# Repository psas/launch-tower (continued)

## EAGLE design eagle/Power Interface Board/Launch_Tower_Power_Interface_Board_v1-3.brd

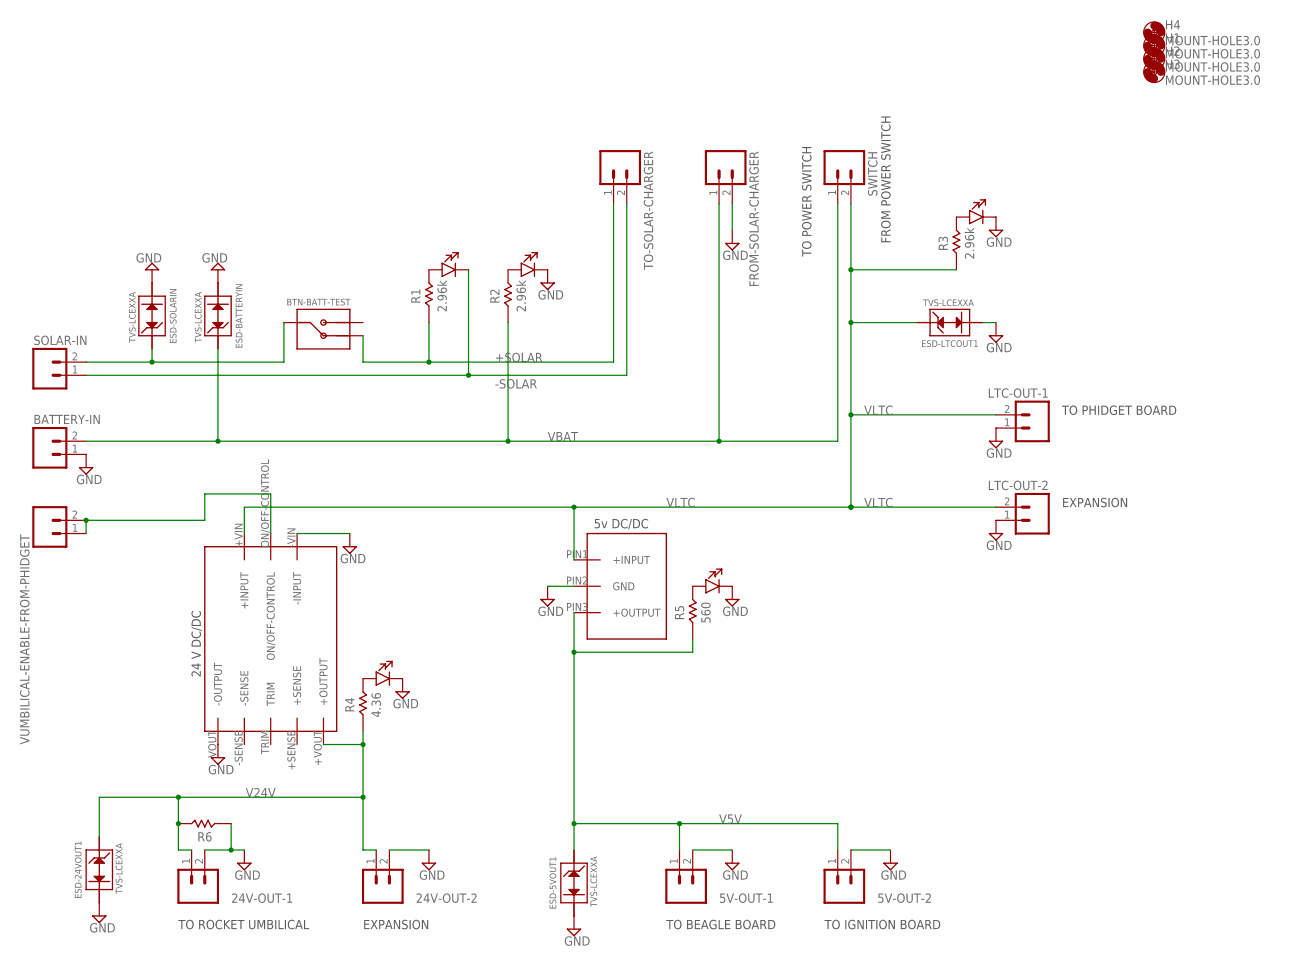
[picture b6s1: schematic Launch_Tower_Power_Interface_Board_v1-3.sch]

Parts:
5V-OUT-1, 5V-OUT-2, 24V-OUT-1, 24V-OUT-2: M025MM; SCREWTERMINAL-5MM-2
BATTERY-IN: M025MM; SCREWTERMINAL-5MM-2
BTN-BATT-TEST: BUTTON-107-3006-EVX; BUTTON-1
ESD-5VOUT1, ESD-24VOUT1: TVS-LCEXXA; D0-201
ESD-BATTERYIN: TVS-LCEXXA; D0-201
ESD-LTCOUT1: TVS-LCEXXA; D0-201
ESD-SOLARIN: TVS-LCEXXA; D0-201
FROM-SOLAR-CHARGER: M025MM; SCREWTERMINAL-5MM-2
H1, H2, H3, H4: MOUNT-HOLE3.0; 3,0
LED-5V-DC/DC, LED-24V-DC/DC: LED-550-XX04; LED-550
LED-BATTERY-IN: LED-550-XX04; LED-550
LED-SOLAR-IN: LED-550-XX04; LED-550
LED-SWITCH-IN: LED-550-XX04; LED-550
LTC-OUT-1, LTC-OUT-2: M025MM; SCREWTERMINAL-5MM-2
R1, R2, R3: 2.96k; 0805
R4: 4.36; 0805
R5: 560; 0805
R6: RESISTOR-0805; 0805
SOLAR-IN: M025MM; SCREWTERMINAL-5MM-2
SWITCH: M025MM; SCREWTERMINAL-5MM-2
TO-SOLAR-CHARGER: M025MM; SCREWTERMINAL-5MM-2
U$1: DC/DC_CONV_24V; UWE
U$2: DC/DC_CONV_5V; OKI-SIP
VUMBILICAL-ENABLE-FROM-PHIDGET: M023.5MM; SCREWTERMINAL-3.5MM-2

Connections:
+SOLAR: BTN-BATT-TEST.NC, R1.ANODE, TO-SOLAR-CHARGER.1
-SOLAR: LED-SOLAR-IN.CATHODE, SOLAR-IN.1, TO-SOLAR-CHARGER.2
GND: 5V-OUT-1.2, 5V-OUT-2.2, 24V-OUT-1.2, 24V-OUT-2.2, BATTERY-IN.1, ESD-5VOUT1.CATHODE, ESD-24VOUT1.CATHODE, ESD-BATTERYIN.CATHODE, ESD-LTCOUT1.CATHODE, ESD-SOLARIN.CATHODE, FROM-SOLAR-CHARGER.2, LED-5V-DC/DC.CATHODE, LED-24V-DC/DC.CATHODE, LED-BATTERY-IN.CATHODE, LED-SWITCH-IN.CATHODE, LTC-OUT-1.1, LTC-OUT-2.1, R6.ANODE, U$1.-VIN (-INPUT), U$1.-VOUT (-OUTPUT), U$2.PIN2 (GND)
GPIO: U$1.ON/OFF-CONTROL, VUMBILICAL-ENABLE-FROM-PHIDGET.1, VUMBILICAL-ENABLE-FROM-PHIDGET.2
unnamed: LED-SOLAR-IN.ANODE, R1.CATHODE
unnamed: LED-BATTERY-IN.ANODE, R2.CATHODE
unnamed: LED-SWITCH-IN.ANODE, R3.CATHODE
unnamed: LED-5V-DC/DC.ANODE, R5.CATHODE
unnamed: LED-24V-DC/DC.ANODE, R4.CATHODE
unnamed: BTN-BATT-TEST.COMMON, ESD-SOLARIN.ANODE, SOLAR-IN.2
V5V: 5V-OUT-1.1, 5V-OUT-2.1, ESD-5VOUT1.ANODE, R5.ANODE, U$2.PIN3 (+OUTPUT)
V24V: 24V-OUT-1.1, 24V-OUT-2.1, ESD-24VOUT1.ANODE, R4.ANODE, R6.CATHODE, U$1.+VOUT (+OUTPUT)
VBAT: BATTERY-IN.2, ESD-BATTERYIN.ANODE, FROM-SOLAR-CHARGER.1, R2.ANODE, SWITCH.1
VLTC: ESD-LTCOUT1.ANODE, LTC-OUT-1.2, LTC-OUT-2.2, R3.ANODE, SWITCH.2, U$1.+VIN (+INPUT), U$2.PIN1 (+INPUT)

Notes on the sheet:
5v DC/DC
TO POWER SWITCH
FROM POWER SWITCH
EXPANSION
TO PHIDGET BOARD
TO BEAGLE BOARD
TO IGNITION BOARD
24 V DC/DC
TO ROCKET UMBILICAL

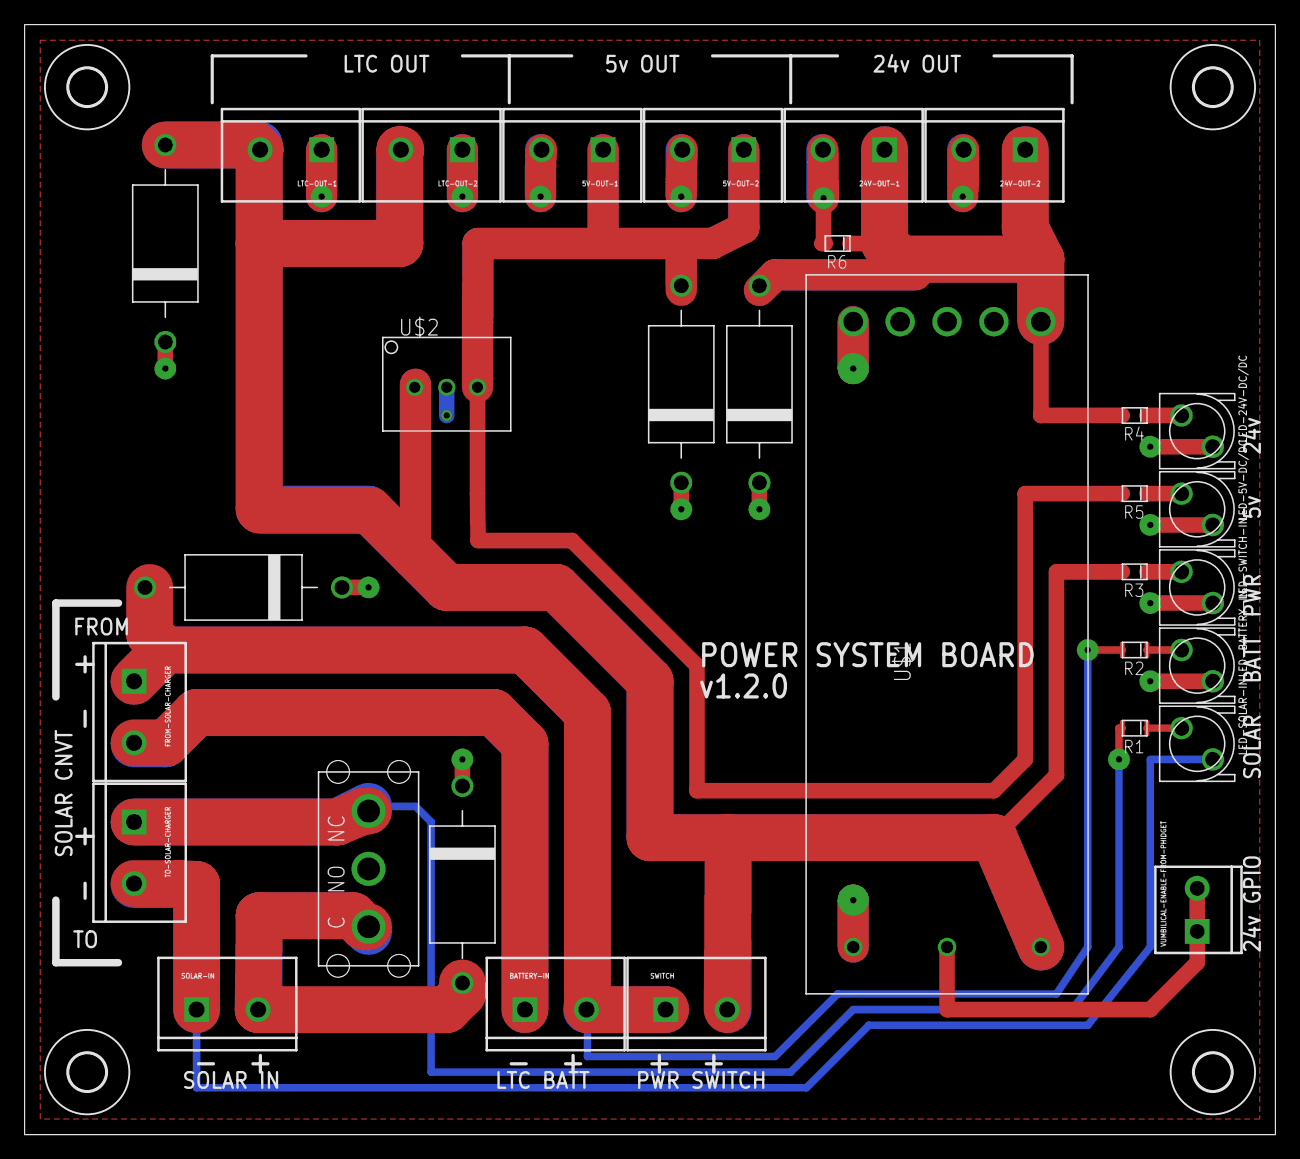
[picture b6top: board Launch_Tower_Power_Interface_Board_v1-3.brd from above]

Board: 2 copper layers, 101.6 x 90.2 mm, 35 parts (0 on the bottom side), 14 nets.

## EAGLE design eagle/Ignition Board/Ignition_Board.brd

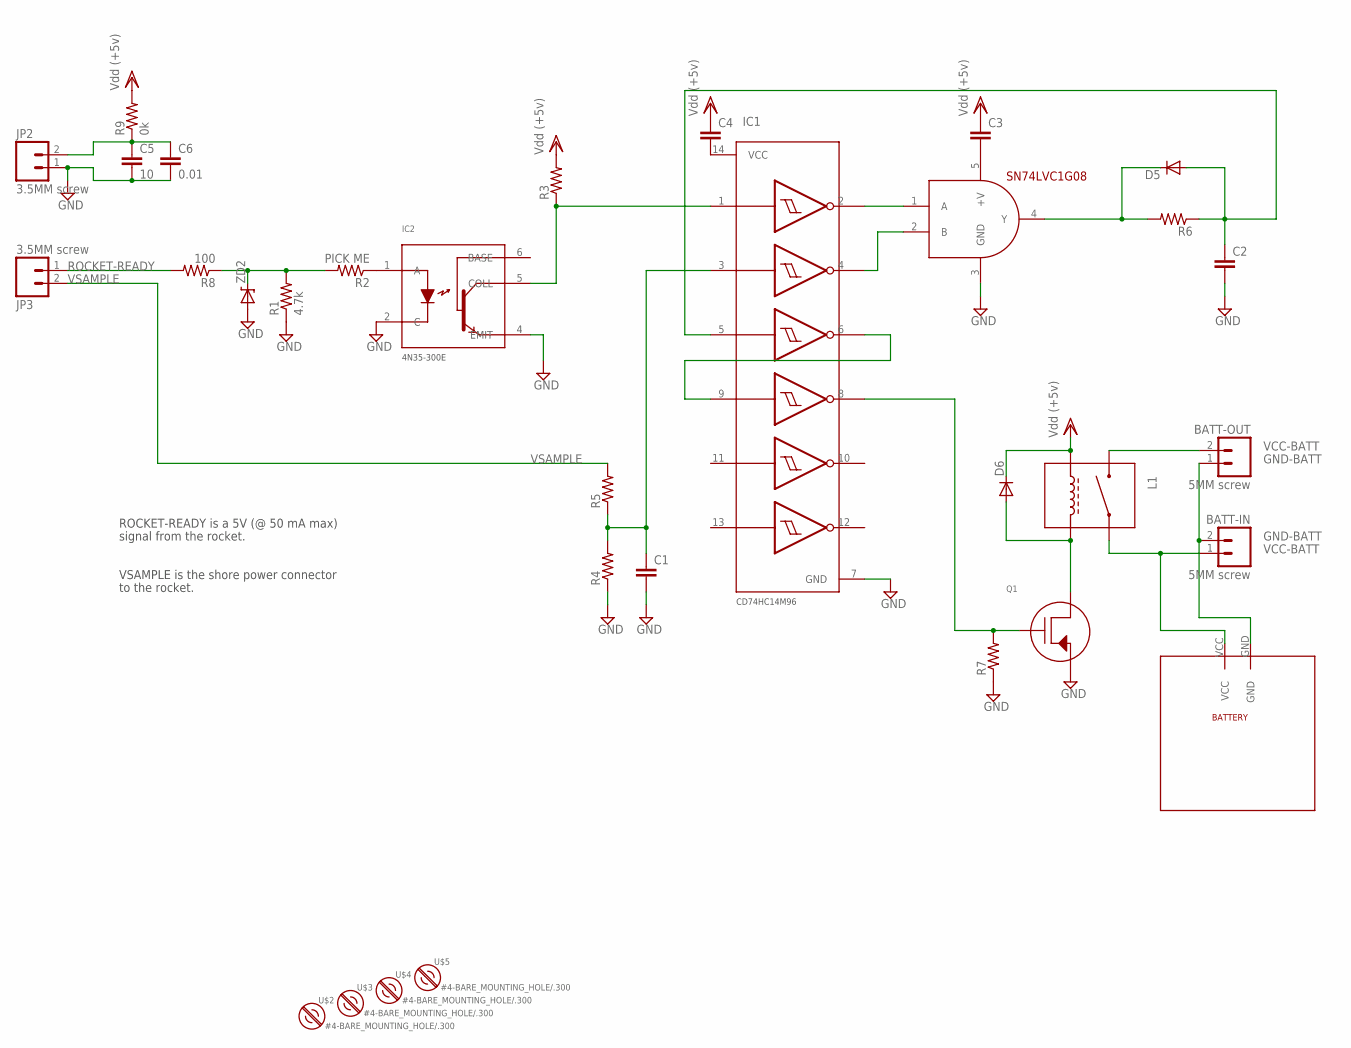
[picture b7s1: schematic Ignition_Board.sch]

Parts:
BATT-IN: 5MM screw; SCREWTERMINAL-5MM-2
BATT-OUT: 5MM screw; SCREWTERMINAL-5MM-2
C1, C2, C3, C4: C-EU0805-B-NOSILK; 0805-B-NOSILK
C5: 10; 0805-B-NOSILK
C6: 0.01; 0805-B-NOSILK
D5, D6: DIODEPTH; DIODE-1N4001
IC1: INVERT GATES; INVERTSOIC14
IC2: OPTOISOLATOR; 4N35-300E
JP2, JP3: 3.5MM screw; SCREWTERMINAL-3.5MM-2
L1: RELAY; G5T-1A
Q1: NMOSFET; FETSO-8
R1: 4.7k; 0805-B-NOSILK
R2: PICK ME; 0805-B-NOSILK
R3, R4, R5, R6, R7: R-US_0805-B-NOSILK; 0805-B-NOSILK
R8: 100; 0805-B-NOSILK
R9: 0k; 0805-B-NOSILK
U$1: AND GATE; SOT23-5
U$2, U$3, U$4, U$5: #4-BARE_MOUNTING_HOLE/.300; #4/.300-BARE+STD_NUT_OR_STAR_WASHER
U$6: BATTERY; BATT-1
ZD2: DIODE-ZENERPTH; DIODE-ZENER

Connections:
GND: C1.2, C2.2, C5.2, C6.2, IC1.7 (GND), IC2.2 (C), IC2.4 (EMIT), JP2.1, Q1.1 (SOURCE), R1.1, R4.1, R7.1, U$1.3 (GND), ZD2.P$2 (A)
GND-BATT: BATT-IN.2, BATT-OUT.1, U$6.GND
unnamed: IC1.4 (2Y), U$1.2 (B)
unnamed: IC1.1 (1A), IC2.5 (COLL), R3.1
unnamed: JP3.1, R8.2
unnamed: IC1.2 (1Y), U$1.1 (A)
unnamed: IC2.1 (A), R2.1
unnamed: C1.1, IC1.3 (2A), R4.2, R5.1
unnamed: C4.2, IC1.14 (VCC)
unnamed: D6.A, L1.CIN, Q1.5 (DRAIN)
unnamed: IC1.8 (4Y), Q1.4 (GATE), R7.2
unnamed: C3.2, U$1.5 (+V)
unnamed: C5.1, C6.1, JP2.2, R9.1
unnamed: D5.C, R6.2, U$1.4 (Y)
unnamed: C2.1, D5.A, IC1.5 (3A), R6.1
N-NOT2: IC1.6 (3Y), IC1.9 (4A)
ROCKET-READY: R1.2, R2.2, R8.1, ZD2.P$1 (C)
VCC-BATT: BATT-IN.1, BATT-OUT.2, L1.SW1, L1.SW2, U$6.VCC
VDD: C3.1, C4.1, D6.C, L1.COUT, R3.2, R9.2
VSAMPLE: JP3.2, R5.2

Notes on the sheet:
ROCKET-READY is a 5V (@ 50 mA max)
signal from the rocket.
VSAMPLE is the shore power connector
to the rocket.

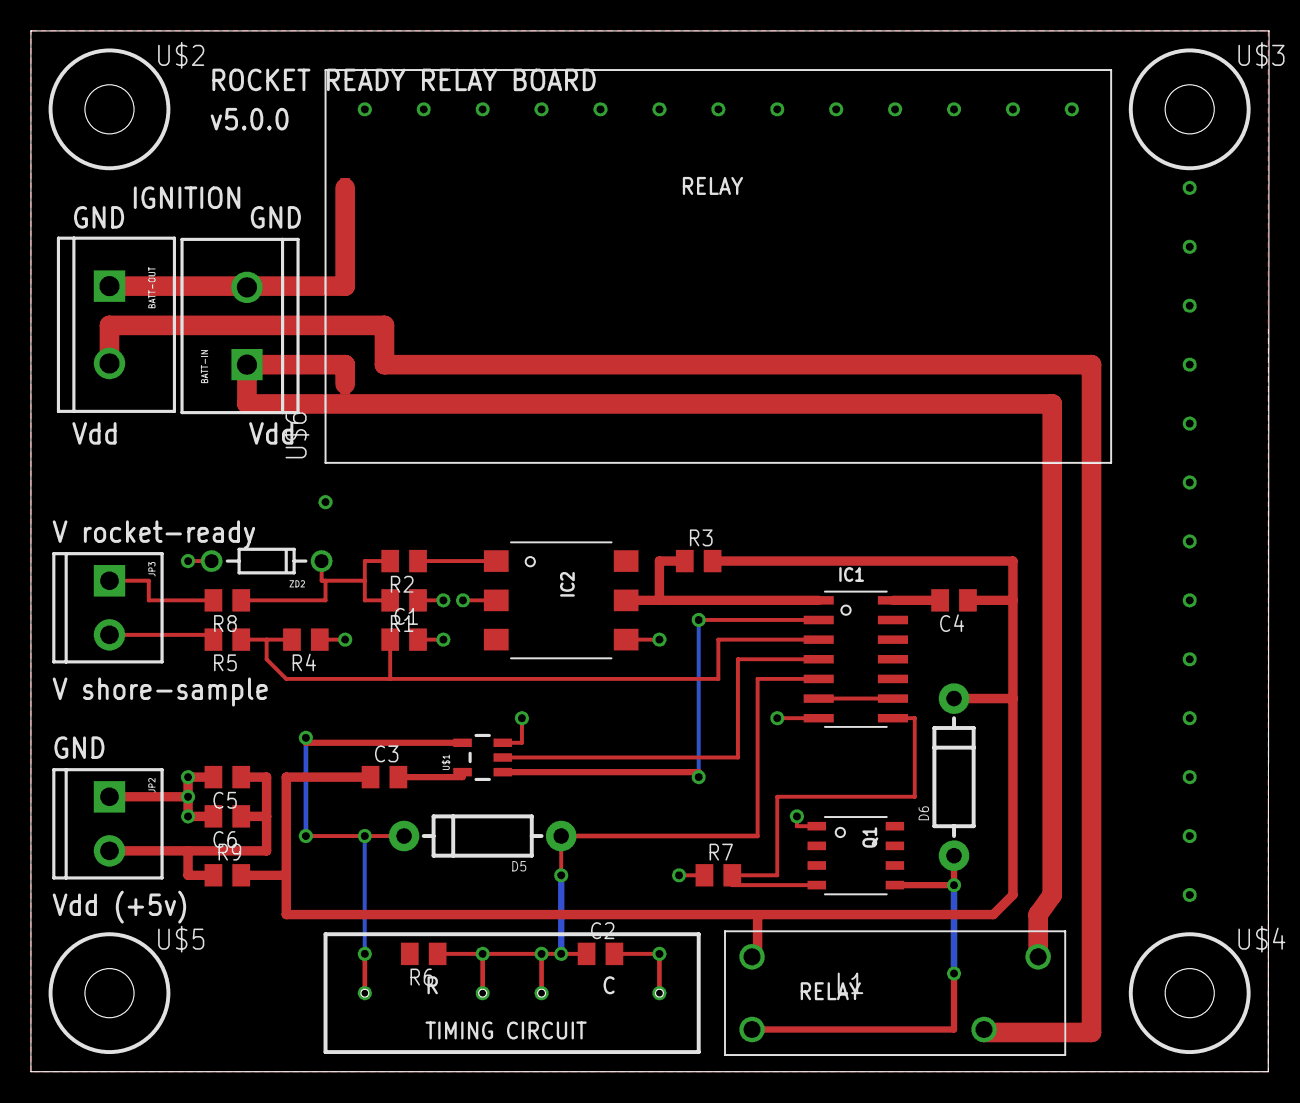
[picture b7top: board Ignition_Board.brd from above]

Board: 2 copper layers, 80.1 x 67.3 mm, 32 parts (0 on the bottom side), 20 nets.

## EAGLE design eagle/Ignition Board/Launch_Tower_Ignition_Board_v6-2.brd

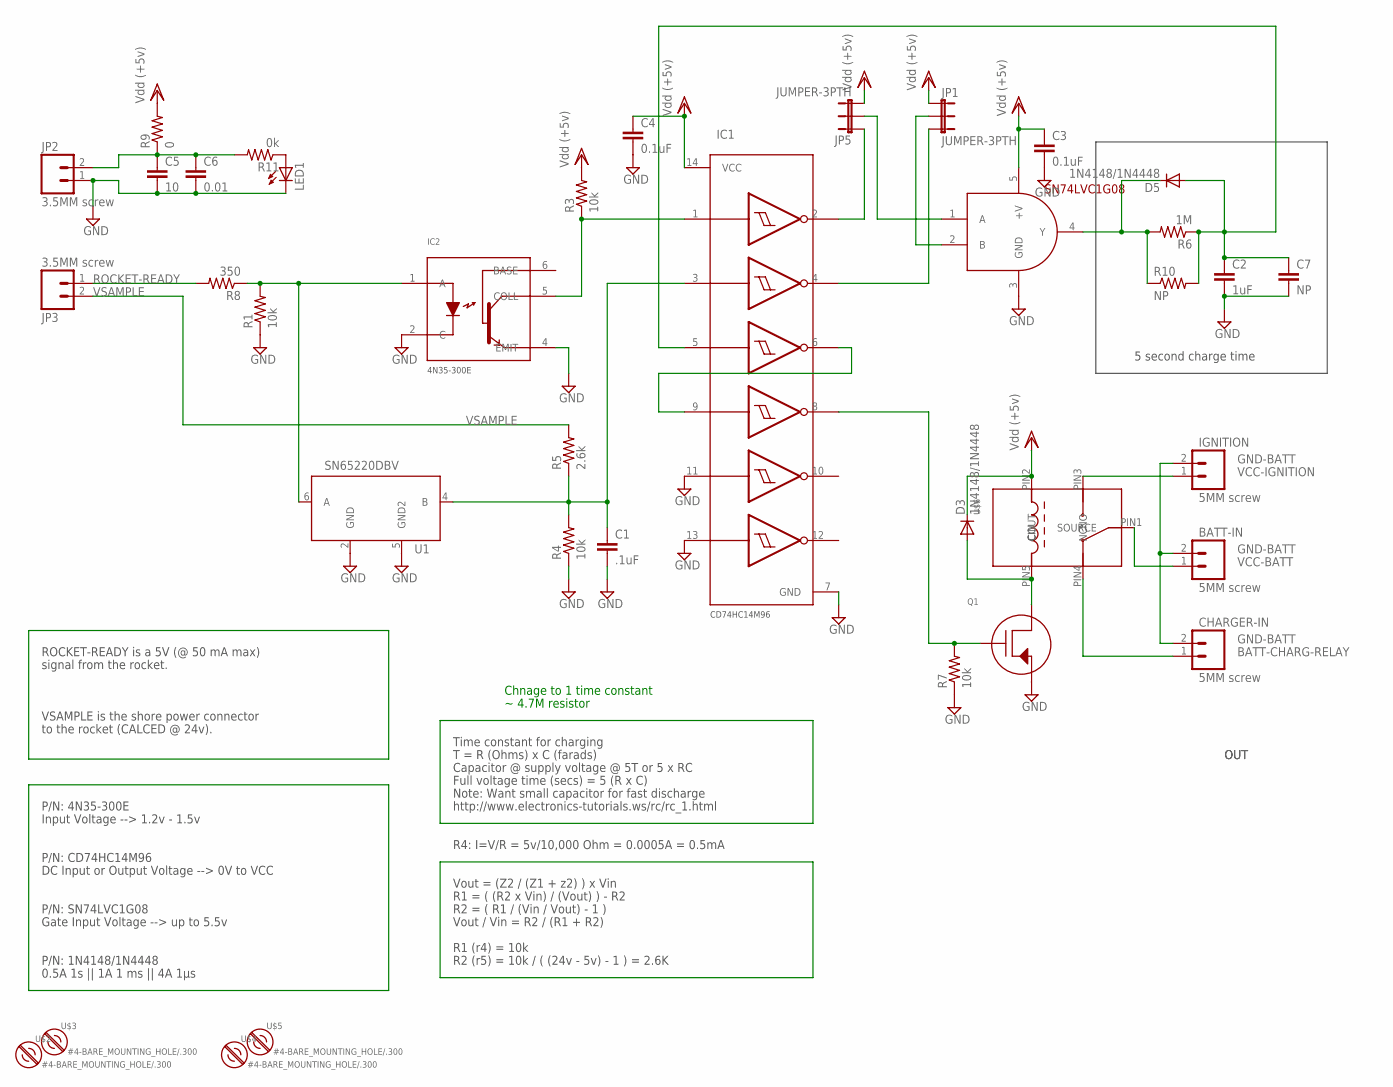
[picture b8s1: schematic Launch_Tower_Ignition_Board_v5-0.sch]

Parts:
BATT-IN: 5MM screw; SCREWTERMINAL-5MM-2
C1: .1uF; 0805-B-NOSILK
C2: 1uF; 0805-B-NOSILK
C3, C4: 0.1uF; 0805-B-NOSILK
C5: 10; 0805-B-NOSILK
C6: 0.01; 0805-B-NOSILK
C7: NP; CAP-PTH-SMALL
CHARGER-IN: 5MM screw; SCREWTERMINAL-5MM-2
D3, D5: 1N4148/1N4448; DIODE-1N4001
IC1: INVERT GATES; INVERTSOIC14
IC2: OPTOISOLATOR; 4N35-300E
IGNITION: 5MM screw; SCREWTERMINAL-5MM-2
JP1, JP5: JUMPER-3PTH; 1X03
JP2, JP3: 3.5MM screw; SCREWTERMINAL-3.5MM-2
LED1: LED-FKIT-1206; FKIT-LED-1206
Q1: NMOSFET; FETSO-8
R1, R3, R4, R7: 10k; 0805-B-NOSILK
R5: 2.6k; 0805-B-NOSILK
R6: 1M; 0805-B-NOSILK
R8: 350; 0805-B-NOSILK
R9: 0; 0805-B-NOSILK
R10: NP; AXIAL-0.4
R11: 0k; 0805-B-NOSILK
U1: SN65220DBV; SOT23-6L
U$1: AND GATE; SOT23-5
U$2, U$3, U$4, U$5: #4-BARE_MOUNTING_HOLE/.300; #4/.300-BARE+STD_NUT_OR_STAR_WASHER
U$6: RELAY-2; G5LA

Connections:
BATT-CHARG-RELAY: CHARGER-IN.1, U$6.PIN4 (NC)
GND: C1.2, C2.2, C3.2, C4.2, C5.2, C6.2, C7.2, IC1.7 (GND), IC1.11 (5A), IC1.13 (6A), IC2.2 (C), IC2.4 (EMIT), JP2.1, LED1.C, Q1.1 (SOURCE), R1.1, R4.1, R7.1, U1.2 (GND), U1.5 (GND2), U$1.3 (GND)
GND-BATT: BATT-IN.2, CHARGER-IN.2, IGNITION.2
unnamed: JP1.2, U$1.2 (B)
unnamed: LED1.A, R11.1
unnamed: IC1.1 (1A), IC2.5 (COLL), R3.1
unnamed: JP3.1, R8.2
unnamed: JP5.2, U$1.1 (A)
unnamed: IC1.4 (2Y), JP1.3
unnamed: C1.1, IC1.3 (2A), R4.2, R5.1, U1.4 (B)
unnamed: D3.A, Q1.5 (DRAIN), U$6.PIN5 (CIN)
unnamed: IC1.8 (4Y), Q1.4 (GATE), R7.2
unnamed: IC1.2 (1Y), JP5.1
unnamed: C5.1, C6.1, JP2.2, R9.1, R11.2
unnamed: D5.C, R6.2, R10.P$1 (1), U$1.4 (Y)
unnamed: C2.1, C7.1, D5.A, IC1.5 (3A), R6.1, R10.P$2 (2)
N-NOT2: IC1.6 (3Y), IC1.9 (4A)
ROCKET-READY: IC2.1 (A), R1.2, R8.1, U1.6 (A)
VCC-BATT: BATT-IN.1, U$6.PIN1 (SOURCE)
VCC-IGNITION: IGNITION.1, U$6.PIN3 (NO)
VDD: C3.1, C4.1, D3.C, IC1.14 (VCC), JP1.1, JP5.3, R3.2, R9.2, U$1.5 (+V), U$6.PIN2 (COUT)
VSAMPLE: JP3.2, R5.2

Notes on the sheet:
ROCKET-READY is a 5V (@ 50 mA max)
signal from the rocket.
VSAMPLE is the shore power connector
to the rocket (CALCED @ 24v).
OUT
R4: I=V/R = 5v/10,000 Ohm = 0.0005A = 0.5mA
Time constant for charging
T = R (Ohms) x C (farads)
Capacitor @ supply voltage @ 5T or 5 x RC
Full voltage time (secs) = 5 (R x C)
Note: Want small capacitor for fast discharge
Vout = (Z2 / (Z1 + z2) ) x Vin
R1 = ( (R2 x Vin) / (Vout) ) - R2
R2 = ( R1 / (Vin / Vout) - 1 )
Vout / Vin = R2 / (R1 + R2)
0.5A 1s || 1A 1 ms || 4A 1μs
R1 (r4) = 10k
Gate Input Voltage --> up to 5.5v
DC Input or Output Voltage --> 0V to VCC
P/N: SN74LVC1G08
P/N: CD74HC14M96
P/N: 4N35-300E
Input Voltage --> 1.2v - 1.5v
R2 (r5) = 10k / ( (24v - 5v) - 1 ) = 2.6K
P/N: 1N4148/1N4448
http://www.electronics-tutorials.ws/rc/rc_1.html
5 second charge time
Chnage to 1 time constant
~ 4.7M resistor

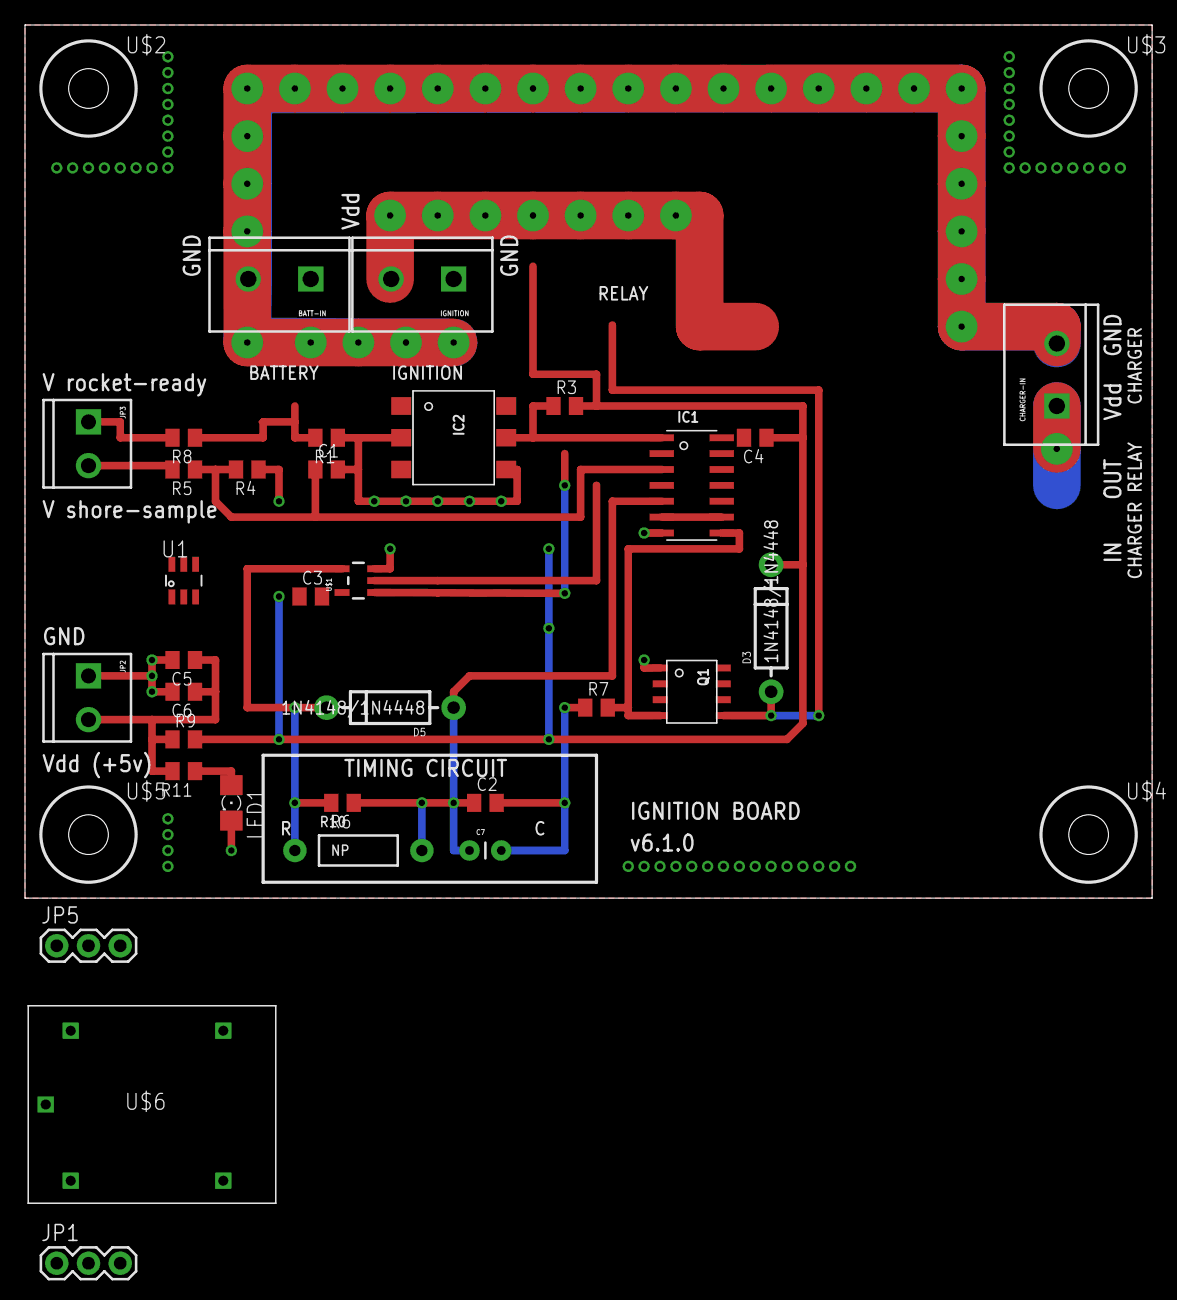
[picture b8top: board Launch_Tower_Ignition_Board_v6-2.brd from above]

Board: 2 copper layers, 90.2 x 69.8 mm, 37 parts (0 on the bottom side), 22 nets.

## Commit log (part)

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2015-01-27 More edits to LTC3 requirements doc.
2015-02-01 Added beginning of LTC2 high-level diagram
2015-02-11 More work on LTC3 power diagram. Still a rough draft.
2015-03-15 Updated LTC3 README.
2015-04-02 More work on LTC3 schematic. 1. Created placeholder "power in" schematic. 2. First cut at external trigger schematic (MOSTFETs and mechanical relays).
2015-04-04 Incremental progress on LTC3 design spec, schematic.
2015-04-09 Another minor design spec correction.
2015-04-18 Updated datasheet collection. Added notes to schematic.
2015-04-25 Datasheet updates. 1. Deleted Cincon DC-DC converter datasheet. 2. Updated TDK-Lambda DC-DC converter datasheet. 3. Updated design spec with links to online TDK docs.
2015-05-16 Modified LTC3 Requirements: removed battery voltage requirement. Battery technology is (more or less) independent of the required power rails, and the team is strongly considering using a battery wit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
2015-05-16 Added some notes for LT8490 configuration
2015-05-30 Added BQ77PL9000 schematic and footprint to libs.
2015-06-10 Working space for charging circuit.
2015-06-13 Very minor adjustments to BeagleBone Cape schematic layout.
2015-06-19 Tidying up ltc3/kicad/ tree.
2015-07-01 More LTC3 design: completed DC-DC converter schematics. Mostly. A thorough review of the PTN78020[WH] datasheet followed by a once-over of the schematic wouldn't hurt.
2015-07-17 Changes in the ltc3/temp/ sub-tree. 1. Added a text file of LTC299x-related notes (I2C V/A/T sensor). 2. Deleted ltc3/temp/kernel-module-ltc2990. It was it's own git repo, and subprojects give me fit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
2015-07-24 Moved voltage/current sense resistors onto DC-DC Converter sheet. From the BeagleBone Cape sheet. This makes the schematics cleaner, as there are fewer hierarchical pins to keep track of.
2015-08-14 Added PDF schematic for LTC2 Eagle ignition board file. Changed name of component configuration docs.
2015-08-26 LTC3: Replaced incorrect EEPROM data sheet with the correct version.
2015-10-01 Added MSOP-16 footprint to ltc3 KiCad files.
2015-10-17 Baby steps towards formal LTC3 project planning.
2015-10-20 Progress on merging master with Charging_Circuit branch.
    Still have plenty of schematic clean-up to perform. There's a lot
    going on around the LT8490.
2015-10-25 Added TODO list to charging circuit page.
2015-10-31 Progress on cleaning up battery management and balance schematics.
2015-11-01 Deleted "Power Sources" sheet.
    Moved what little circuity it contained into the "Battery Charging"
    and "Battery Balancing" sheets.
2015-11-04 Added datasheets on weather/environment-resistant Ethernet connectors.
2015-11-07 LTC3: Renamed LT8705 datasheet file.
2015-11-08 LTC3: Added lab power input to batt mgmt schematic.
2015-11-14 LTC3: Mostly completed ignition control schematic.
2015-11-17 LTC3: Tidied up rocket interface schematic.
2015-11-22 Combined external power and trigger sheets.
    Still need to make the page pretty.
2015-11-22 LTC3: Added datasheet for TI bq77PL900 demo board.
    Contains a useful schematic of a working bq77-based circuit.
2015-11-22 LTC3: Renamed DC/DC converter-enabling hierachical pins.
2015-11-26 LTC3: Reordered schematic sub-sheets; updated PDF export of schematic.
    KiCad has an odd habit of ordering a schematic's sub-sheets without
    notice.
2015-12-12 LTC3: Minor edits to battery charging, balance sheets.
2015-12-15 LTC3: Minor cosmetic edits to rocket/ignition sheet.
2015-12-16 LTC3: Progress on rocket/ignition schematic.
    1. Fixed mis-wired relay diodes.
    2. Completed ignition relay circuitry.
    3. Began work on umbilical connector circuitry.
2015-12-16 LTC3: Progress on charging schematic.
    1. Merged Andy's updates to the battery charging schematic. Thanks,
    Andy!
    2. Re-annotated entire schematic; updated PDF.
2015-12-22 Added note section to heirarchical schematics. Added path to ground on DC-DC converters. Replaced thermistor with 'duct tape' 0 ohm resistor on BQL77PL900.
2015-12-29 LTC3: Began replacing Schottky OR diodes w/ "ideal" diodes.
    Created schematic symbol for TI LM74610-Q1 ideal/smart diode
    controller. Added relevant data sheets.
    Began implementing the circuitry that will replace the existing
    Schottky input diodes in the battery charging schematic. Left my work
    off to the left hand side of the page. Still need to complete and
    integrate with the charging circuitry.
2016-01-09 LTC3: More progress on prettifying the battery charger schematic.
2016-01-16 LTC3: Cleaned up battery charging and BeagleBone interface sheets.
2016-01-22 Deleted garbage file(s).
2016-01-30 LTC3: Replaced thermistor/0R on charger and balance schematics w/ connector.
    Each to be connected to an off-board NTC thermistor taped to the
    battery pack.
2016-02-07 LTC3: Minor adjustments, many comments from today's design review.
2016-02-10 LTC3: Updated PDF of schematic.
2016-02-13 LTC3: Deleted broken *cache.lib.
2016-02-17 Set all i2c on a single bus, added notes section, finished to do's, clarified important questions.
2016-02-19 LTC3: Standardized optoisolator selection.
    Replaced the Avago 4N35 on the ignition control schematic with the
    Toshiba TLP3542 used on the external power and triggers schematic.
    This reduces the number of unique parts used in the design. The Avago
    has an order of magnitude faster switching time than the Toshiba, but
    that shouldn't matter for the ignition control circuit; the Toshiba's
    2.5A max current is way more than sufficient.
2016-02-20 Updated DC-DC Converters and Beaglebone Sheets.
    *Added test points to both sheets.
    *Added a switch array for manual overrides on DC-DC converters page.
    *Removed finished ToDo's
2016-03-05 LTC3: Added rocket umbilical state detection to ignition sub-sheet.
2016-03-12 LTC3: Minor Changes to Battery Management -Removed unnecessary resistors on MOSFET gates -Added pin connector for EEPROM on BQ77PL900 -Changed resistor on LT8490 switch pins
2016-03-12 LTC3: Added test points; hid test point and ground symbol values.
    1. Added single-node test points to bq77PL900 VOUT and IOUT pins;
    included a ground test point nearby.
    2. Set all test point and ground symbols' value fields to invisible.
2016-03-26 LTC3: Deleted _autosave* file; updated .gitignore.
2016-04-02 LTC3: Fixed mis-oriented diodes in battery management schematic.
2016-04-11 Assigned component footprints.
2016-04-16 Really this time.
2016-04-16 LTC3: Minor fixes to test points in batt. balance schematic.
    Also updated netlist, schematic PDF.
2016-04-23 LTC3: Added off-board (front panel) connectors for external power and trigger circuits.
    Plus an inconsequential amount of PCB layout.
2016-04-30 LTC3: Schematic style policing and miscellaneous prettification.
    Completed all sheets but DC-DC converters and ignition control.
    Also updated netlist and schematic PDF export.
2016-05-08 LTC3: Fixes, clean-ups...
    1. Removed inverters from DC-DC converters' INHIBIT pin circuitry.
    Renamed node labels accordingly.
    2. Moved zero-volt charging FET on bq sheet. It was wired to bypass
    the discharge FETs, and should be bypassing the charge FETS.
    3. Added connectors between board and igntion external interfaces
    (breaker, arming switch, shorting bar, ignition power).
2016-05-09 LTC3: Minor cosmetic adjustment to ignition schematic.
2016-05-12 LTC3: More footprint assignment.
    Set footprint to "OFF-BOARD" for all off-board components. This
    results in an error dialog when opening the footprint assignment tool,
    but it makes it obvious which components shouldn't have any footprint
    assigned.
2016-05-15 LTC3: Reannotated schematic.
    Power nodes were mysteriously annotated incorrectly again.
2016-05-29 LTC3: Layout Work
    Guess what? More layout work! (still on the power section)
2016-06-08 LTC3: Made use of corrected bq footprint.
2016-06-15 LTC3: Added pin annotations to PTN78020[WH] footprint.
2016-06-16 LTC3: Fixed mis-named pin in VIN power node symbol.
2016-06-26 LTC3: Split single-board design into two boards.
    Separated the charge controller and cell protection circuitry onto its
    own board (kicad/charge_controller). The DC-DC converters,
    BeagleBone, external power and triggers, and ignition fire control
    circuitry remains together (kicad/ltc).
    Both boards have had their schematics updated. Sub-sheets for
    circuitry moved to the other board were removed. Still more work
2016-06-29 LTC3: Copied KiCad fp-lib-table into each board's sub-directory.
    Symlinks don't seem to work properly on Windows.
2016-06-29 LTC3: Moved the Coilcraft datasheet to the appropriate sub-directory.
2016-07-01 LTC3: LT8490 Layout
    Some final changes and preparation for LT8490 layout.
2016-07-06 LTC3: Layout Con't
    I spent like 5 minutes on this commit and got kind of frustrated. Not
    much in here.
2016-07-09 LTC3: Created footprint for mounting hole sized for a #4 screw.
2016-07-12 LTC3: Rev 0.1 of LTC3 Charge Controller Layout
    Finished new revision of LTC3 charge controller layout, featuring:
    -giant inductor footprint (squid)
    -mounting holes
    -thermal relief turned off for Vin
    -Vout connector
    -surface mount LEDs
2016-07-16 LTC3: Charge controller work.
    1. Added low-current DC rail connector (5V, 3.3V).
    2. Adde mfg name and part numbers for all resistors.
2016-07-16 LTC3: Layout Work/Connector Updating
    Added many needed connectors and added to layout.
    -Added 5V nodes for Charge Controller/Cell Protection
    -Added I2C bus connectors
    -Added Vin connectors for Cell Protection
    Added all connectors to layout and ensured all nodes were connected.
2016-07-22 LTC3: More LTC layout work
    Came to a rough finale of the LTC board layout.
2016-08-30 LTC3: More Charge Controller BOM selection.
2016-09-04 LTC3: Replaced DC-DC converters' individual switches with a single switch.
    One main power switch now enables all three converters.
    Added pin header to each converter's nINHIBIT pin to facilitate manual
    control.
2016-09-04 LTC3: Modified LTC DC-DC converter schematic.
    Added voltage dividers to both sides of LTC299x current sense
    resistors.
2016-09-04 LTC3: Modified LTC ignition control schematic.
    Gave ignition battery ground node a distinctive symbol.
2016-09-05 LTC3: Update to charge controller schematic/PCB
    -Adjusted resistors on charge controller for better current limiting
    -Changed footprints of current sense resistors
    -Began adjusting layout, making the board slightly larger
2016-09-06 LTC3: One last correction to charge controller BOM.
    And I'm serious this time.
2016-09-07 LTC3 Cell Protection Layout
    Reworked layout with changes to schematic and various footprints.
    Also added via stapling.
2016-09-08 LTC3 Cell Protection Layout
    A little bit of work on the silk screen for the board layout.
    We moved the temp sensing to off board, do we still want footprints for
    these on the cell protection board?
2016-09-08 LTC3: Minor changes to Charge Controller BOM.
    Nothing that impacts PCB layout.
2016-09-08 LTC3: Modified LTC BOM, schematic.
    1. Added footprints for mechanical relays. (PCB layout already had
    correct footprint; but incorrect annotation.)
    2. Created footprint for RJ-45 jack. This impacts the existing PCB
    layout.
2016-09-09 LTC3 Layout
    Minor changes to charge controller PCB.
2016-09-10 LTC3: Added mechanical drawing of Dialight LED indicators.
2016-09-13 LTC3: Doubled pin count of LTC's DC in and ignition battery connectors.
    Using the same 4-pin Molex MicroFit as used for battery connection on
    Charge Controller and Cell Protection boards.
2016-09-13 LTC3: LTC BOM and PCB changes.
    1. Added RJ45 connector outline to BeagleBone footprint.
    2. Rotated BeagleBone footprint on PCB, so that the RJ45 connector
    is on a board edge.
    3. Added a notch to the board for BeagleBone RJ45 jack clearance.
    4. Updated PCB footprint annotations to align with changes made to the
    LTC schematic in the past few months.
2016-09-15 LTC3: Some Pretty Dang Close Layout Updates
    It's working again, hooray! Pushing everything from the layout review
    yesterday. May give them a look over later this afternoon as well and
    export gerbers for the LTC board.
2017-02-09 Deleted old Gerber files.
2019-02-09 Updated LTC3 to-do list.
2019-03-08 Replaced old schematic PDFs with new KiCad v5 versions.
